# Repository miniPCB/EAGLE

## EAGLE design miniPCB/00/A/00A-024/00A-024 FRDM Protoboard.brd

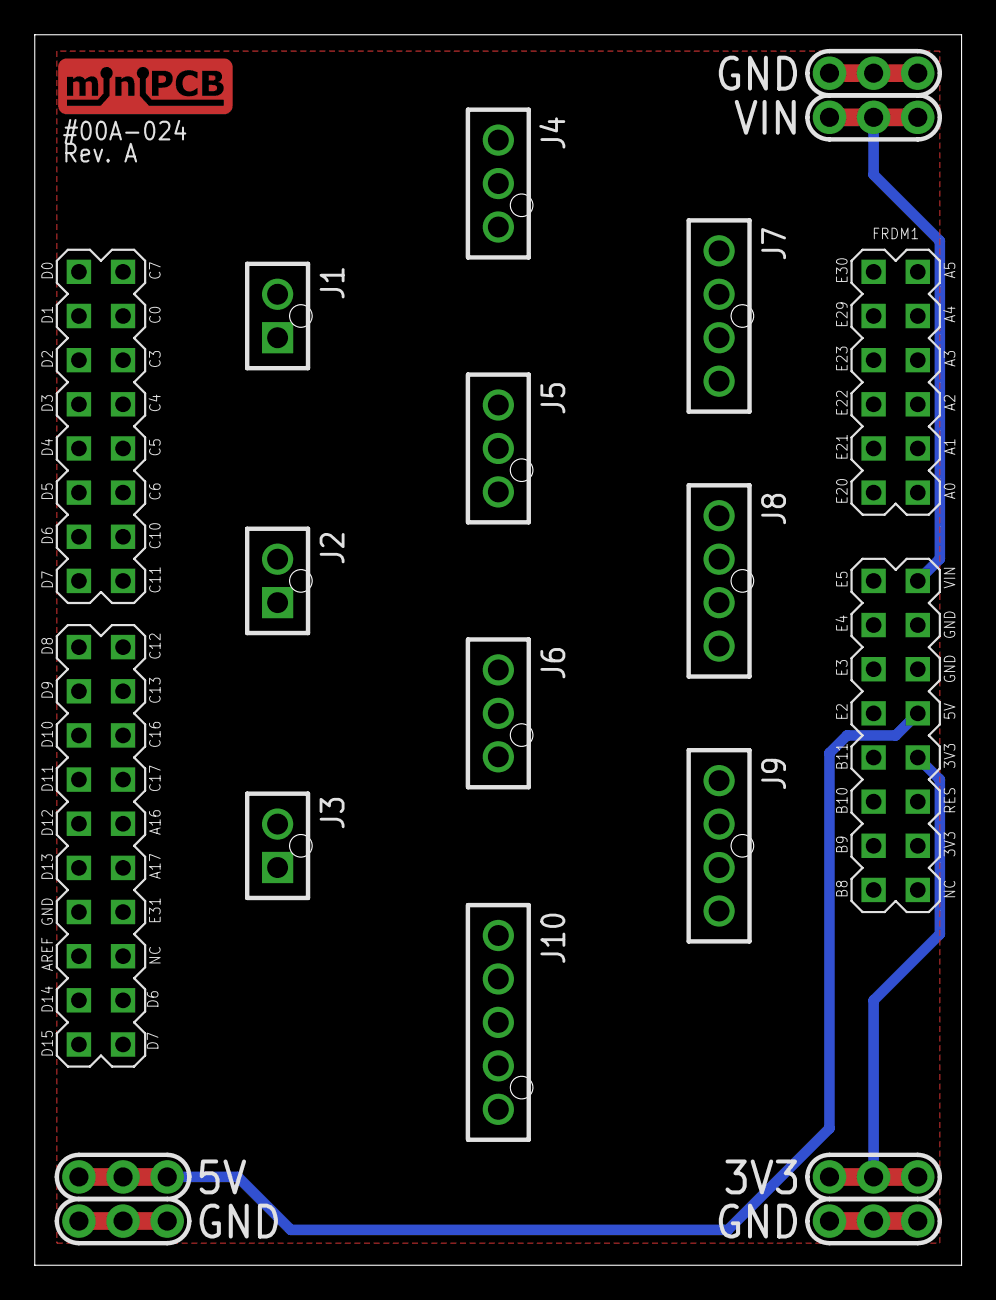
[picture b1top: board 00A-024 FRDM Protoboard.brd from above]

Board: 2 copper layers, 53.3 x 70.8 mm, 18 parts (0 on the bottom side), 4 nets.

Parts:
FRDM1: FRDM-KL25ZNORMAL; FRDM_KL25Z_NORMAL
J1, J2, J3: PINS_2-NANOFIT-105309-1102; PINS_2-NANOFIT
J4, J5, J6: PINS_3-NANOFIT-105309-1103; PINS_3-NANOFIT
J7, J8, J9: PINS_4105309-1104; PINS_4-NANOFIT
J10: PINS_5105309-1105; PINS_5-NANOFIT
P57: 3V3; PINS_1-3P_VALUE
P58: 5V; PINS_1-3P_VALUE
P59: VIN; PINS_1-3P_VALUE
P102, P103, P114: GND; PINS_1-3P_VALUE
U$1: MINIPCB_LOGO; MINIPCB-LOGO

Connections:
GND: FRDM1.GND0, FRDM1.GND1, FRDM1.GND2, P102.1, P102.2, P102.3, P103.1, P103.2, P103.3, P114.1, P114.2, P114.3
unnamed: FRDM1.P3V3, P57.1, P57.2, P57.3
unnamed: FRDM1.5V, P58.1, P58.2, P58.3
unnamed: FRDM1.VIN, P59.1, P59.2, P59.3

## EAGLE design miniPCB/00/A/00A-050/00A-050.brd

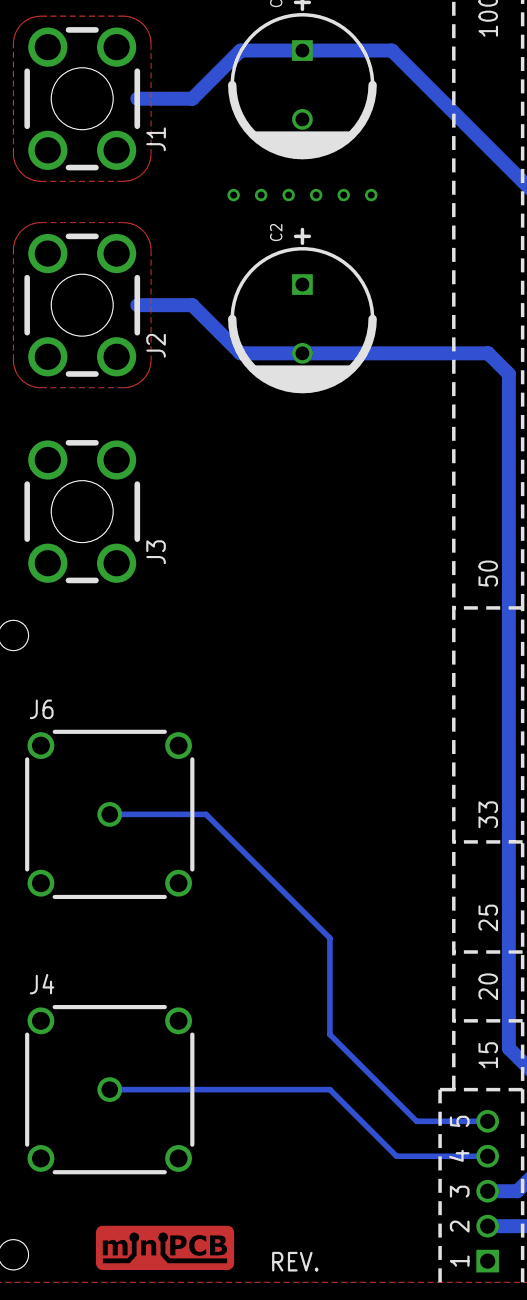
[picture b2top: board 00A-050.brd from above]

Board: 2 copper layers, 9 parts (0 on the bottom side), 5 nets.

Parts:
C1, C2: C5MM
J1: +V; SCREW-TERMINAL-M3
J2: -V; SCREW-TERMINAL-M3
J3: GND; SCREW-TERMINAL-M3
J4: IN.A; B35N14H
J5: SLOT: A; MINIPCB_DOCK_5P
J6: OUT.A; B35N14H
PCB: MINIPCB_DOCK_50X100

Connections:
GND: C1.-, C2.+, J3.1, J3.2, J3.3, J3.4, J4.2.GND, J4.3.GND, J4.4.GND, J4.5.GND, J5.1, J6.2.GND, J6.3.GND, J6.4.GND, J6.5.GND
unnamed: J4.1.SIG, J5.4
unnamed: J5.5, J6.1.SIG
V+: C1.+, J1.1, J1.2, J1.3, J1.4, J5.2
V-: C2.-, J2.1, J2.2, J2.3, J2.4, J5.3

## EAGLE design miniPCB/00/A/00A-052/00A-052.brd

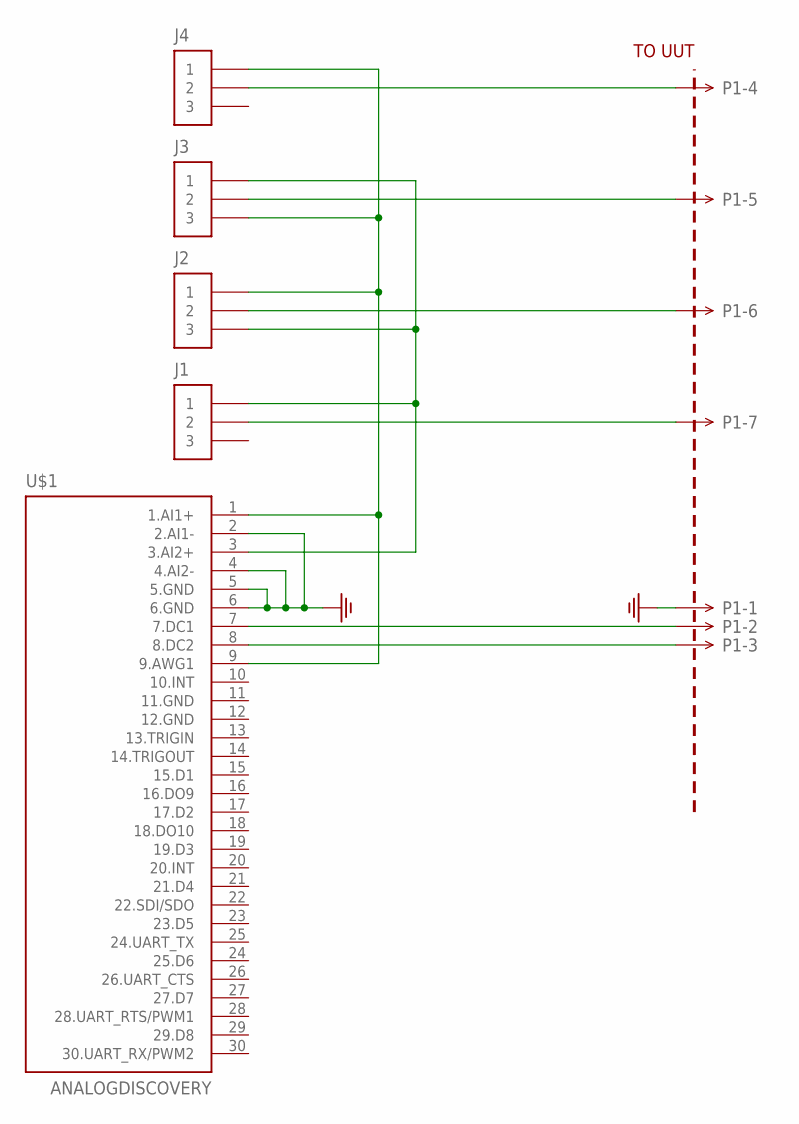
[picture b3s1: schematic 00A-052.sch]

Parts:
J1, J2, J3, J4: PINS_3_2.54; PINS_3
P1: MINIPCB_7P; PINS_1X7
PCB1: TO UUT; MINIPCB_0P_25X50; PART_NUMBER 00A-052
U$1: ANALOGDISCOVERY; PINS30-2X15

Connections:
GND: P1.1, U$1.2 (2.AI1-), U$1.4 (4.AI2-), U$1.5 (5.GND), U$1.6 (6.GND)
unnamed: P1.2, U$1.7 (7.DC1)
unnamed: P1.3, U$1.8 (8.DC2)
unnamed: J1.2, P1.7
unnamed: J2.2, P1.6
unnamed: J3.2, P1.5
unnamed: J4.2, P1.4
unnamed: J1.1, J2.3, J3.1, U$1.3 (3.AI2+)
unnamed: J2.1, J3.3, J4.1, U$1.1 (1.AI1+), U$1.9 (9.AWG1)

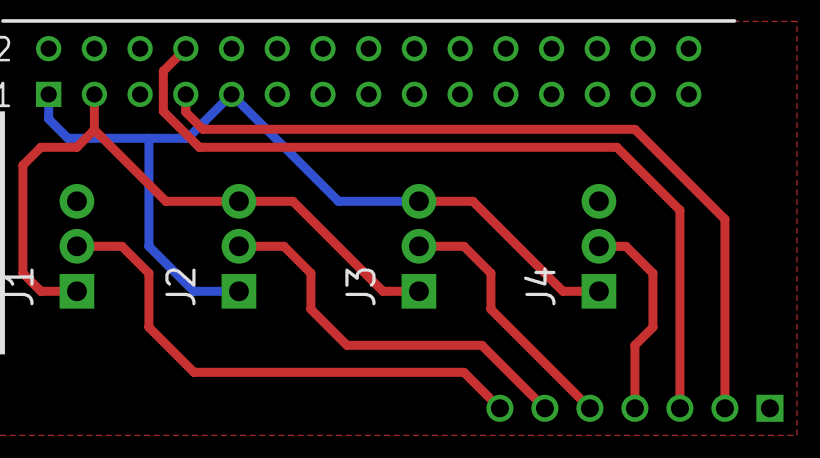
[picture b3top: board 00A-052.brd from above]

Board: 2 copper layers, 7 parts (0 on the bottom side), 9 nets.

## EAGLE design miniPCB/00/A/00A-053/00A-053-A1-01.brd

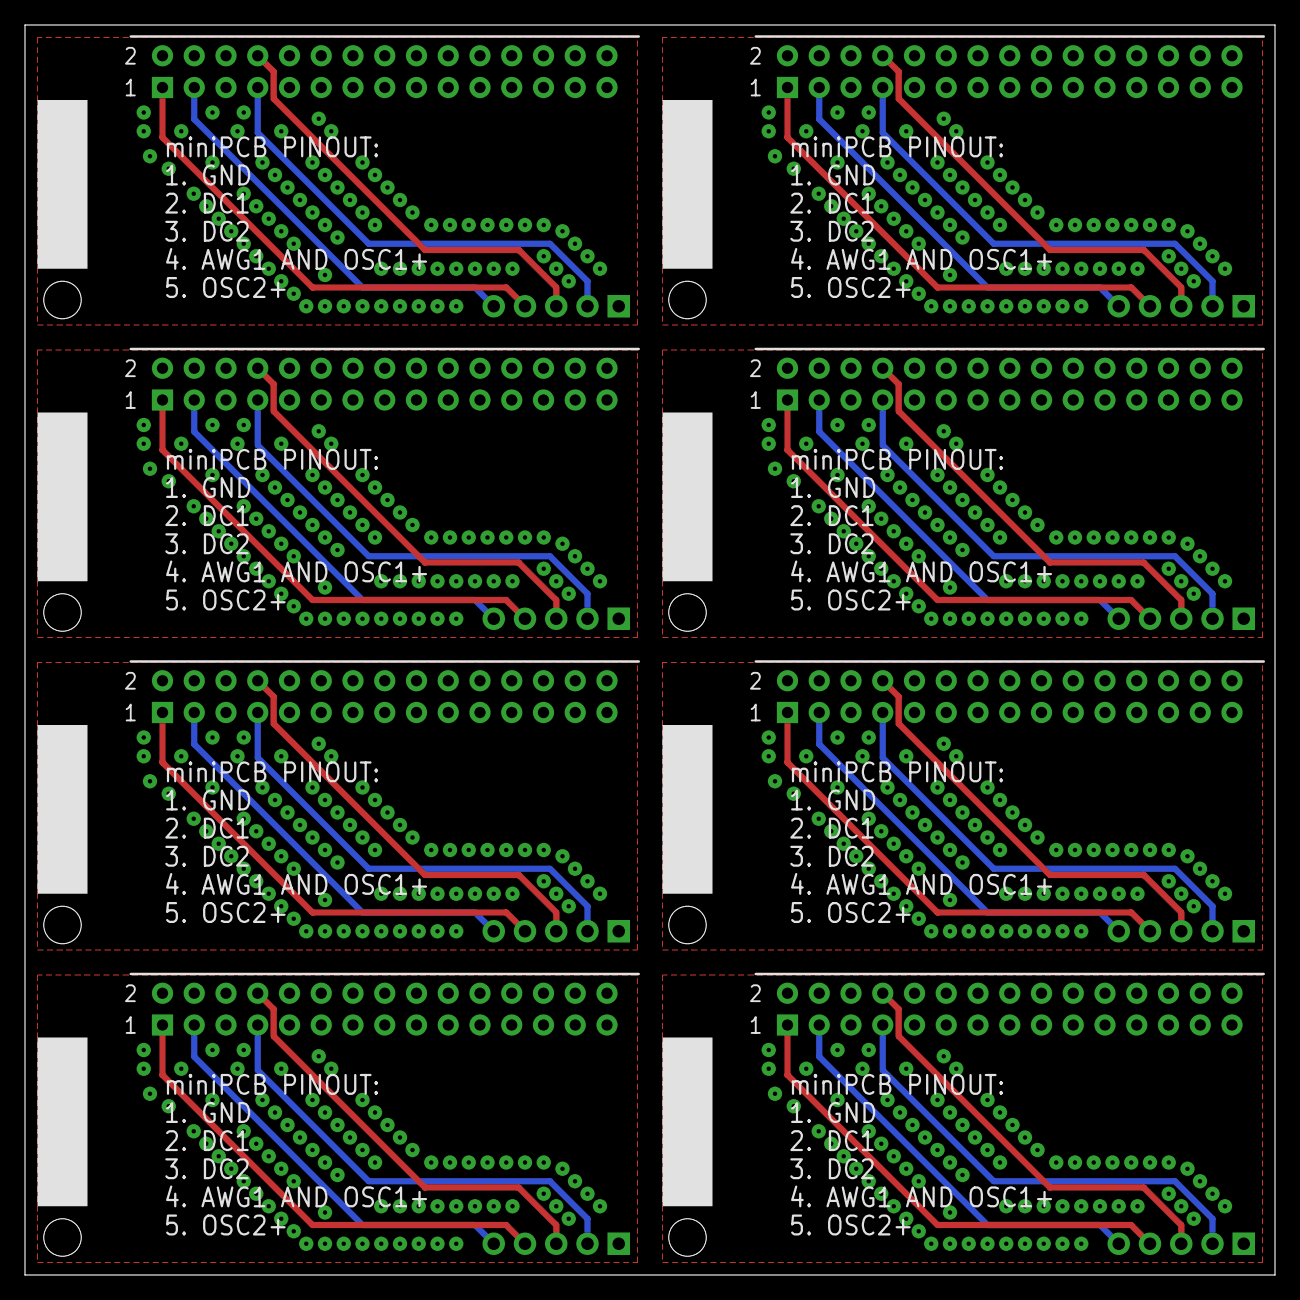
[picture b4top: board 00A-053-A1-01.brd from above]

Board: 2 copper layers, 100.0 x 100.0 mm, 25 parts (0 on the bottom side), 40 nets.

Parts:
E$1: MINIPCB_PANEL_IMAGEFRAME
P1, P2, P3, P4, P5, P6, P7, P8: PINS_1X5
PCB1, PCB2, PCB3, PCB4, PCB5, PCB6, PCB7, PCB8: MINIPCB_0P_25X50
U$1, U$2, U$3, U$4, U$5, U$6, U$7, U$8: ANALOGDISCOVERY; PINS30-2X15

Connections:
GND: P1.1, U$1.2, U$1.4, U$1.5, U$1.6, U$1.11, U$1.12
GND1: P2.1, U$2.2, U$2.4, U$2.5, U$2.6, U$2.11, U$2.12
GND2: P3.1, U$3.2, U$3.4, U$3.5, U$3.6, U$3.11, U$3.12
GND3: P4.1, U$4.2, U$4.4, U$4.5, U$4.6, U$4.11, U$4.12
GND4: P5.1, U$5.2, U$5.4, U$5.5, U$5.6, U$5.11, U$5.12
GND5: P6.1, U$6.2, U$6.4, U$6.5, U$6.6, U$6.11, U$6.12
GND6: P7.1, U$7.2, U$7.4, U$7.5, U$7.6, U$7.11, U$7.12
GND7: P8.1, U$8.2, U$8.4, U$8.5, U$8.6, U$8.11, U$8.12
unnamed: P1.5, U$1.3
unnamed: P1.4, U$1.1
unnamed: P1.2, U$1.7
unnamed: P1.3, U$1.8
unnamed: P2.5, U$2.3
unnamed: P2.4, U$2.1
unnamed: P2.2, U$2.7
unnamed: P2.3, U$2.8
unnamed: P3.5, U$3.3
unnamed: P3.4, U$3.1
unnamed: P3.2, U$3.7
unnamed: P3.3, U$3.8
unnamed: P4.5, U$4.3
unnamed: P4.4, U$4.1
unnamed: P4.2, U$4.7
unnamed: P4.3, U$4.8
unnamed: P5.5, U$5.3
unnamed: P5.4, U$5.1
unnamed: P5.2, U$5.7
unnamed: P5.3, U$5.8
unnamed: P6.5, U$6.3
unnamed: P6.4, U$6.1
unnamed: P6.2, U$6.7
unnamed: P6.3, U$6.8
unnamed: P7.5, U$7.3
unnamed: P7.4, U$7.1
unnamed: P7.2, U$7.7
unnamed: P7.3, U$7.8
unnamed: P8.5, U$8.3
unnamed: P8.4, U$8.1
unnamed: P8.2, U$8.7
unnamed: P8.3, U$8.8

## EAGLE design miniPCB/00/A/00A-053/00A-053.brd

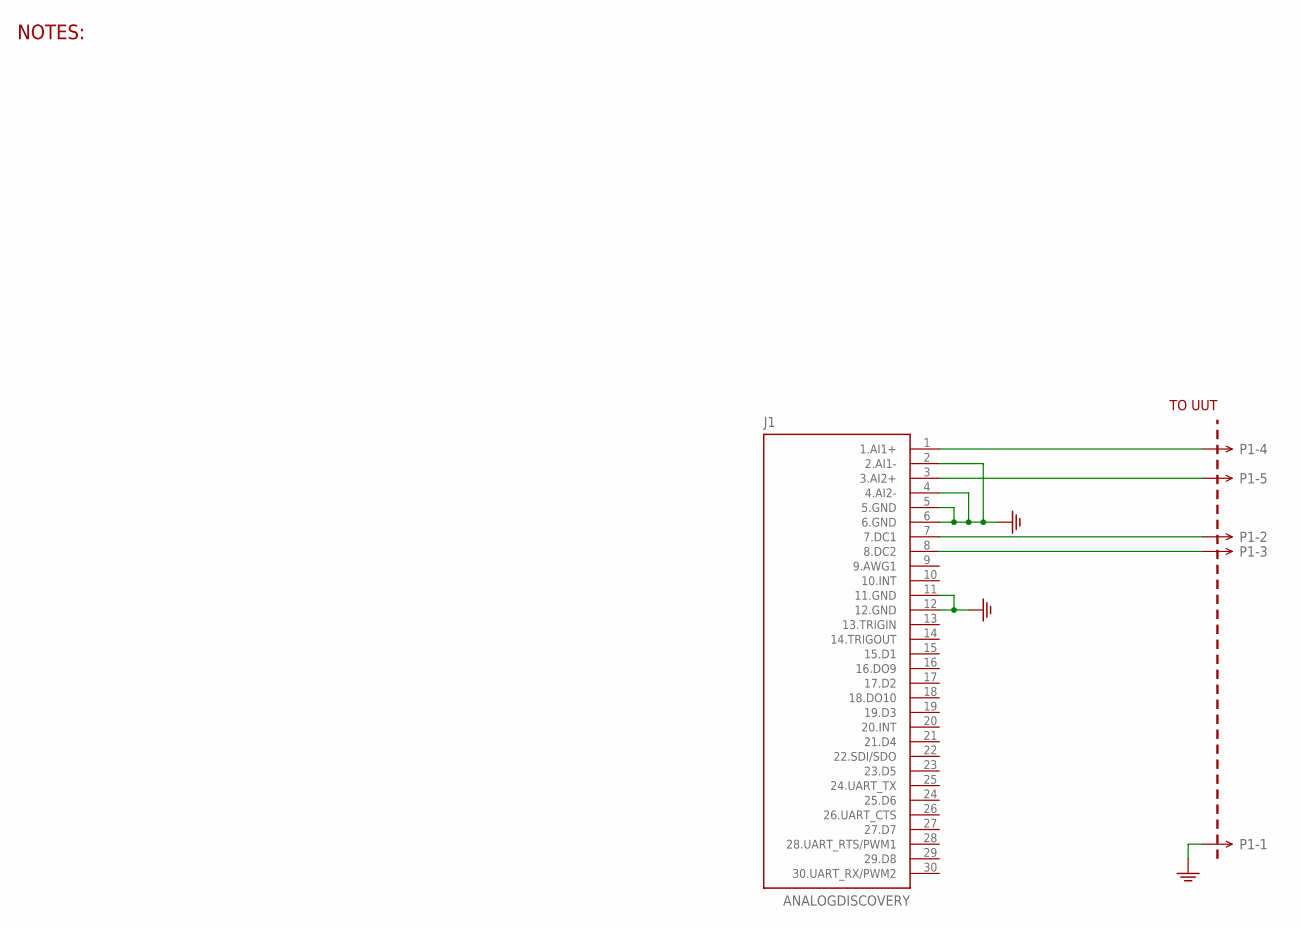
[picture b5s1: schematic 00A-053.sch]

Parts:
J1: ANALOGDISCOVERY; PINS30-2X15
P1: MINIPCB_5P5P; PINS_1X5
PCB1: MINIPCB_0P25X50; MINIPCB_0P_25X50; PART_NUMBER 00A-053

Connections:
GND: J1.2 (2.AI1-), J1.4 (4.AI2-), J1.5 (5.GND), J1.6 (6.GND), J1.11 (11.GND), J1.12 (12.GND), P1.1
unnamed: J1.3 (3.AI2+), P1.5
unnamed: J1.1 (1.AI1+), P1.4
unnamed: J1.7 (7.DC1), P1.2
unnamed: J1.8 (8.DC2), P1.3

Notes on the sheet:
NOTES:

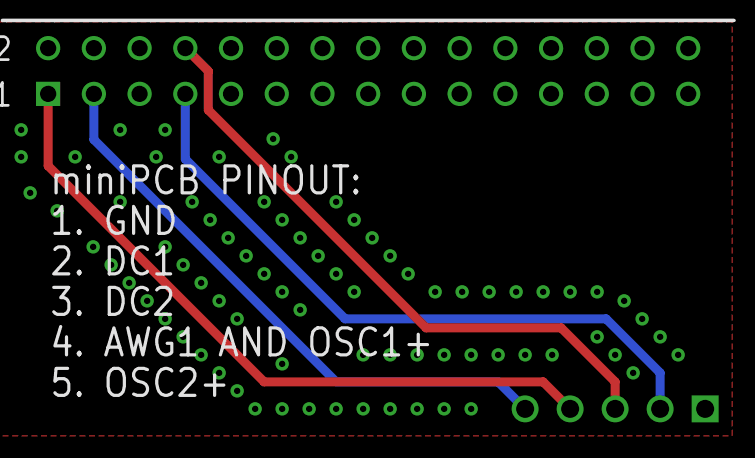
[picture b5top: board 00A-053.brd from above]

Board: 2 copper layers, 3 parts (0 on the bottom side), 5 nets.

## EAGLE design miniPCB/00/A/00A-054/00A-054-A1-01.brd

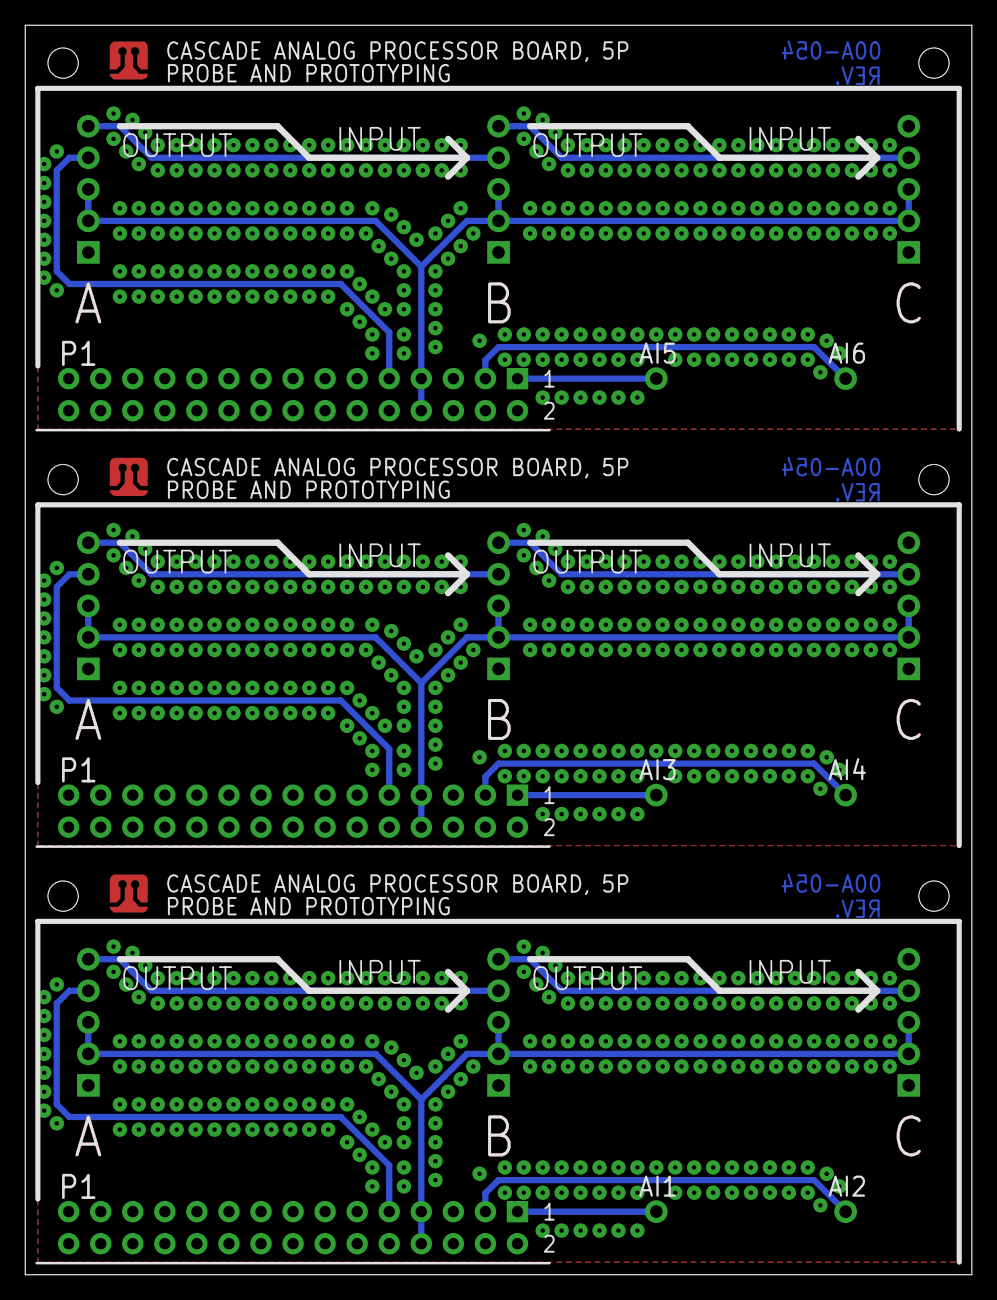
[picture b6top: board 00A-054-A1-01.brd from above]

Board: 2 copper layers, 75.0 x 99.0 mm, 22 parts (0 on the bottom side), 21 nets.

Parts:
AI1, AI2, AI3, AI4, AI5, AI6: PINS_1_TESTPOINT_KE5000_NOTEXT
E$1: MINIPCB_PANEL_IMAGEFRAME
P1, P2, P3, P4, P5, P6, P7, P8, P9: PINS_1X5
PCB1, PCB2, PCB3: MINIPCB_0P_33X75
U$1, U$2, U$3: ANALOGDISCOVERY; PINS30-2X15

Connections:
GND: P1.1, P2.1, P3.1, U$1.2, U$1.4, U$1.5, U$1.6
GND1: P4.1, P5.1, P6.1, U$2.2, U$2.4, U$2.5, U$2.6
GND2: P7.1, P8.1, P9.1, U$3.2, U$3.4, U$3.5, U$3.6
unnamed: AI1.1, U$1.1
unnamed: AI2.1, U$1.3
unnamed: P1.4, U$1.9
unnamed: P1.5, P2.4
unnamed: P2.5, P3.4
unnamed: AI3.1, U$2.1
unnamed: AI4.1, U$2.3
unnamed: P4.4, U$2.9
unnamed: P4.5, P5.4
unnamed: P5.5, P6.4
unnamed: AI5.1, U$3.1
unnamed: AI6.1, U$3.3
unnamed: P7.4, U$3.9
unnamed: P7.5, P8.4
unnamed: P8.5, P9.4
V+: P1.2, P1.3, P2.2, P2.3, P3.2, P3.3, U$1.7, U$1.8
V+1: P4.2, P4.3, P5.2, P5.3, P6.2, P6.3, U$2.7, U$2.8
V+2: P7.2, P7.3, P8.2, P8.3, P9.2, P9.3, U$3.7, U$3.8

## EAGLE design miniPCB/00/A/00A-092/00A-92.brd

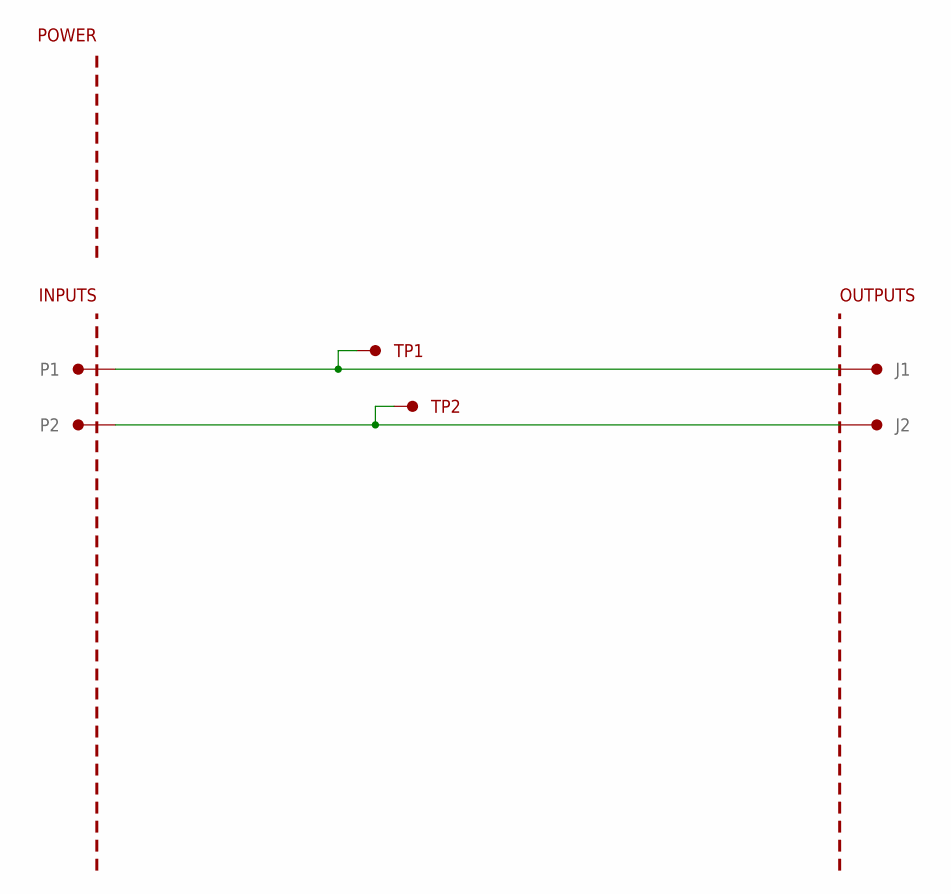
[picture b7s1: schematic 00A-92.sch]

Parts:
J1, J2: PINS_1KE6060; PINS_1_KE6060
P1, P2: PINS_124AWG-NOTEXT; PINS_1_1MM-NOTEXT
PCB1: MINIPCB_0P00A-20X33; MINIPCB_00A_20X33; PART_NUMBER 00A-92-A1-01
TP1, TP2: TESTPOINTKE5000-SMTEXT; PINS_1_TESTPOINT_KE5000_NOTEXT

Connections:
unnamed: J1.1, J1.2, P1.1, P1.2, TP1.1
unnamed: J2.1, J2.2, P2.1, P2.2, TP2.1

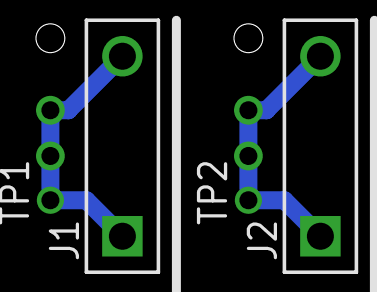
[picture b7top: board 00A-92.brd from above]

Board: 2 copper layers, 7 parts (0 on the bottom side), 2 nets.
